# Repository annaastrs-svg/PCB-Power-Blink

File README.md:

Power Blink  ;)
---
A power bank PCB Module designed in KiCAD, to safly charge lithium battery and u can look in the display the battery percentage on the oled screen
o m g 

Power blink charges though USB-C and delivers power though USB-A, with an onboard fuel gauge and microcontroller driving a small OLED display that shows the actuall battery charge level :B 

BTW BTW BTW low key look at my [JOURNAL.MD WOOWOWOWOWOWWOWOOOO!](https://github.com/annaastrs-svg/PCB-Power-Blink/blob/Pcb/Journal.md)

KiCAD
--
Esquematico
--

PCB
--

3D VIEW 
--

PCB Huellas 
---

CAD
---

 CAD detailes :
 
 The PCB is 55.8067 mm long & 40.9582 tall so i added 2 mm in all sides so it can fit in 

 the button is 6x6 mm
 
 the oled is 5.584 & 22.384 long
 
 the entry of c 14.4 long 
 
 the entry of a is 8.94 cm long 
 
 (btw ignore the pcb it was a scratch )

[look CAD file ](https://github.com/annaastrs-svg/PCB-Power-Blink/tree/Pcb/CAD)

BOM 
---
[BOM file ](https://github.com/annaastrs-svg/PCB-Power-Blink/blob/Pcb/Documentation/BOM.csv)

| Component | Purpose | Qty | Price | link|
|---|---|---|---|---|
| LiPo Battery 3.7V | Fuente de energía principal | 1 | ~$2.29 | i alrdy have one lolazo |
| TP4056-42-ESOP8 | IC de carga | 1 | ~$0.09 | [LCSC C16581](https://www.lcsc.com/product-detail/Battery-Management-ICs_TOPPOWER-Nanjing-Extension-Microelectronics-TP4056-42-ESOP8_C16581.html) |
| DW01A-G | Controlador de protección | 1 | ~$0.07 | [LCSC C61503](https://www.lcsc.com/product-detail/C61503.html) |
| FS8205A | MOSFETs de protección | 1 | ~$0.03 | [LCSC C908265](https://www.lcsc.com/product-detail/MOSFETs_FUXINSEMI-FS8205A_C908265.html) |
| MAX17048G+T10 | Fuel gauge (I2C) | 1 | ~$1.34 | [LCSC C2682616](https://www.lcsc.com/product-detail/C2682616.html) |
| ATtiny1614-SSN | Microcontrolador | 1 | ~$1.67 | [LCSC C614832](https://www.lcsc.com/product-detail/Microcontroller-Units-MCUs-MPUs-SOCs_Microchip-Tech-ATTINY1614-SSN_C614832.html) |
| MT3608 | Boost converter a 5V | 1 | ~$0.11 | [LCSC C84817](https://www.lcsc.com/product-detail/C84817.html) |
| USB-C Receptacle (Hroparts) | Entrada de carga | 1 | ~$0.10 | [LCSC C165948](https://www.lcsc.com/product-detail/C165948.html) |
| USB-A Receptacle THT | Salida de energía | 1 | ~$0.15 | genérico, cualquier tienda |
| OLED 0.91" I2C SSD1306 | Pantalla de batería | 1 | ~$1.20 | [AliExpress](https://www.aliexpress.com/item/33024849277.html) |
| Pulsador momentáneo 6mm | Despertar pantalla | 1 | ~$0.05 | genérico |
| SS34 Schottky | Diodo del boost | 1 | ~$0.05 | genérico |
| LEDs indicadores (CHRG/STDBY) | Indicadores de carga | 2 | ~$0.02 ea. | genérico |
| Resistencias SMD (varias) | 5.1k, 4.7k, 2.4k, 470, 1k, 10k, 75k | 10 | ~$0.01 ea. | genérico |
| Capacitores SMD (10-22µF) | Desacople/filtro | 6 | ~$0.03 ea. | genérico |

**Estimated Total: ~$8.00 USD (sin batería yey )**

## Connection table
[also look at the connection table](https://github.com/annaastrs-svg/PCB-Power-Blink/blob/Pcb/Documentation/Tabla%20de%20Conexiones.csv)

| Componente | Pin | → | Componente | Pin |
|---|---|---|---|---|
| J3 (USB-C) | VBUS | → | U8 (TP4056) | VCC |
| J3 (USB-C) | CC1, CC2 | → | GND | (vía R1, R2 5.1k) |
| U8 (TP4056) | CE | → | VCC | |
| U8 (TP4056) | CHRG | → | LED D2 | → VCC |
| U8 (TP4056) | STDBY | → | LED D1 | → VCC |
| U8 (TP4056) | PROG | → | GND | (vía 2.4k) |
| U8 (TP4056) | BAT | → | +BATT (raw) | |
| Batería | + | → | Q1 (FS8205A) | S1 |
| Batería | − | → | GND | |
| Q1 (FS8205A) | S2 | → | −BATT | |
| Q1 (FS8205A) | G1 | → | U3 (DW01A) | OD |
| Q1 (FS8205A) | D1/D2 | → | U3 (DW01A) | CS (vía R6 1k) |
| Q1 (FS8205A) | G2 | → | U3 (DW01A) | OC |
| U3 (DW01A) | VCC | → | +BATT | (vía R5 470) |
| U3 (DW01A) | GND | → | −BATT | |
| U4 (MAX17048) | VDD | → | +BATT | |
| U4 (MAX17048) | GND | → | GND | |
| U4 (MAX17048) | SDA, SCL | → | Bus I2C | (compartido con U5, U6) |
| U5 (ATtiny1614) | VDD | → | +BATT | |
| U5 (ATtiny1614) | GND | → | GND | |
| U5 (ATtiny1614) | PA1 | → | Bus I2C | SDA |
| U5 (ATtiny1614) | PA2 | → | Bus I2C | SCL |
| U5 (ATtiny1614) | PA3 | → | SW1 | (botón) |
| U5 (ATtiny1614) | PA0/UPDI | → | J2 | Header de programación |
| Bus I2C | SDA, SCL | → | GND | (vía R9, R10 4.7k a +BATT) |
| U6 (OLED) | VCC | → | +BATT | |
| U6 (OLED) | GND | → | GND | |
| U6 (OLED) | SDA, SCL | → | Bus I2C | |
| U1 (MT3608) | IN | → | +BATT | |
| U1 (MT3608) | GND | → | GND | |
| U1 (MT3608) | SW | → | L1, D3 | → VOUT |
| U1 (MT3608) | FB | → | R7 (10k)/R8 (75k) | divisor |
| U1 (MT3608) | EN | → | +BATT | |
| J1 (USB-A) | VBUS | → | VOUT | |
| J1 (USB-A) | D+, D− | → | (puenteados entre sí) | |
| J1 (USB-A) | GND | → | GND | |

TUTORIAL & HOW DOES ITR WORK? HUH 
--

Open the Power Blinck file, the schematic, and the PCB in KiCad.
The symbols and footprints of the components are not included by default in KiCAS, but I attached the footprints and symbols in the PCB files. 
Add them as a library before opening the project, run the ERC and DRC to make sure everything is clean. 
To manufacture, use the Gerber files; they can be uploaded directly to PCBWay and like that :B

The circuit is divided into 4 blocks. The input and charging part is the USB-C, which receives the charge, and the TP4056, which safely charges the battery. (TP4056 SAFE)

The battery and protection section, with the DW01A and FS8205A, protects the cell against overcharge, overdischarge, and short circuits. (DW01A , FS8205A PROTECTS )

The monitoring is done by the MAX17048, which measures the battery percentage, and the ARINY1614, which displays it on the OLED screen. (MAX17048 MEASURE , ARINY1614 READS AND SHOW  )

The power output is the MT3608, which boosts the battery voltage to a stable 5V for the USB-A port. (MT3608 STABLE VOLTAGES)

i loved making this pcb cus it looks easy but at the moment u see a lot of chips/modules with a lot of pins u cant avoid panic
in my projects i struggle a lot with power distribution and this had helpped me a lot :B 

PCB WAY 
--
THIS IS THE V.1 OF THE PROJECT !! (I did it 2 times cus i didnt like v.1)

This is V.2 in PCB basics simulation of the pcb :B 

NOTES
---
This project was made for [MACONDO](https://macondo.hackclub.com/dashboard)

ill improve this project, there some things that ill change, maybe chips, modules or somthing like that. if u want to do this lil tutorial dont get mad at me if it doesnt work lolazo, Im 80 % sure it works !!

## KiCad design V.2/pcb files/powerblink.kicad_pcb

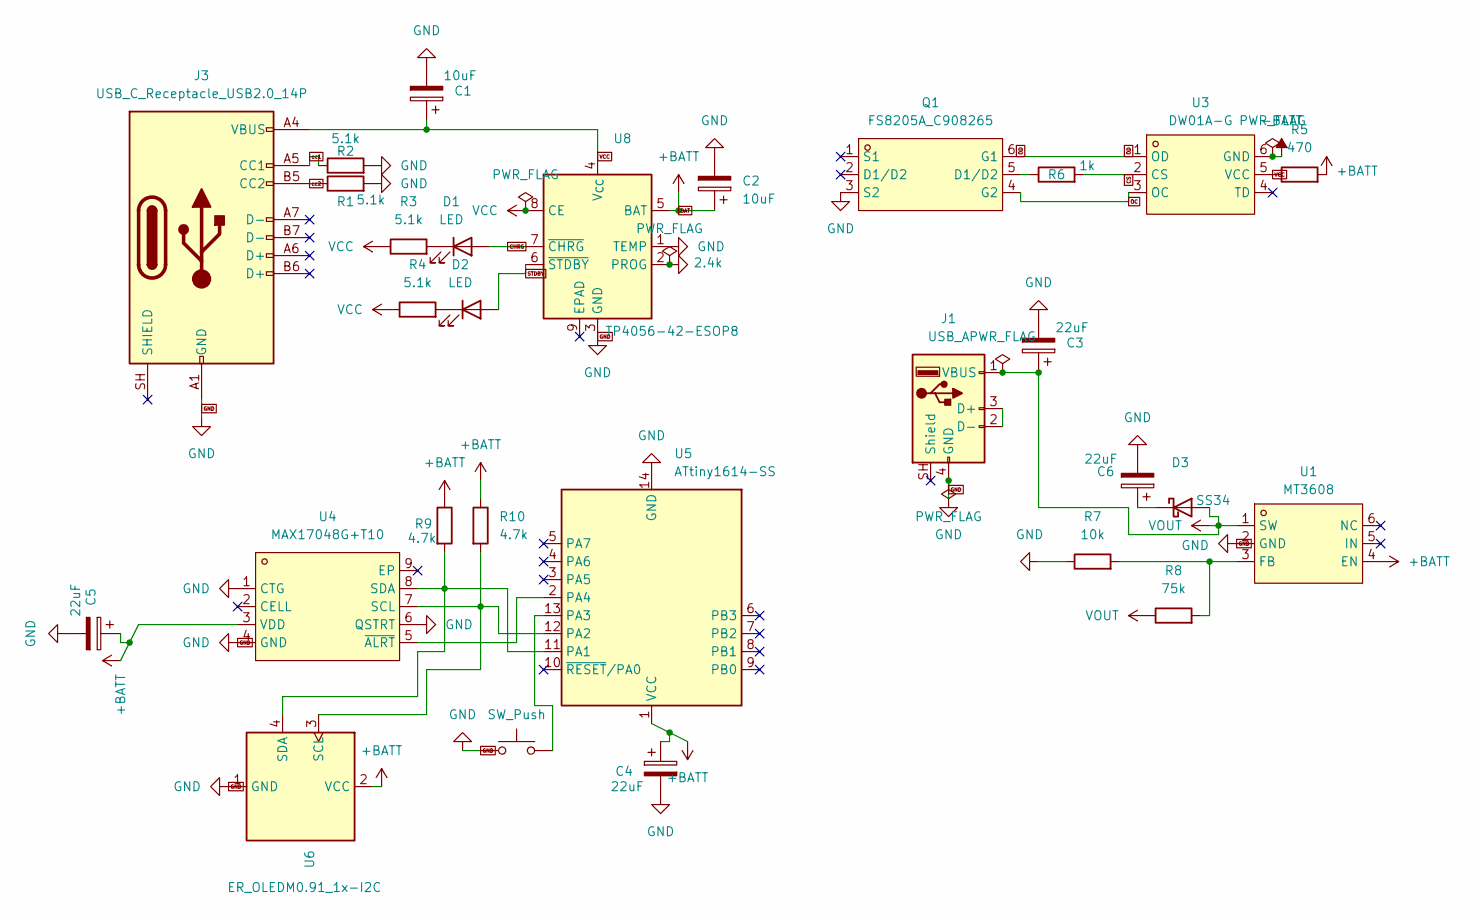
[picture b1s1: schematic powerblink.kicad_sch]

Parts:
C1, C2: 10uF; C_0805_2012Metric
C3, C4, C5, C6: 22uF; C_0805_2012Metric
D1, D2: LED; LED_0603_1608Metric
D3: SS34; D_SMA
J1: USB_A; USB3_A_Molex_48393-001
J3: USB_C_Receptacle_USB2.0_14P; USB_C_Receptacle_HRO_TYPE-C-31-M-12
Q1: FS8205A_C908265; SOT-23-6_L2.9-W1.6-P0.95-LS2.8-BR; MPN FS8205A; LCSC Part C908265
R1, R2, R3, R4: 5.1k; R_0603_1608Metric
R5: 470; R_0603_1608Metric
R6: 1k; R_0603_1608Metric
R7: 10k; R_0603_1608Metric
R8: 75k; R_0603_1608Metric
R9, R10: 4.7k; R_0603_1608Metric
SW1: SW_Push; SW_PUSH_6mm
U1: MT3608; SOT-23-6_L2.9-W1.6-P0.95-LS2.8-BL; MPN MT3608; LCSC Part C84817
U3: DW01A-G; SOT-23-6_L2.9-W1.6-P0.95-LS2.8-BR; MPN DW01A-G; LCSC Part C61503
U4: MAX17048G+T10; TDFN-8_L2.0-W2.0-P0.50-BL-EP1.2; MPN MAX17048G+T10; LCSC Part C2682616
U5: ATtiny1614-SS; SOIC-14_3.9x8.7mm_P1.27mm
U6: ER_OLEDM0.91_1x-I2C
U8: TP4056-42-ESOP8; SOIC-8-1EP_3.9x4.9mm_P1.27mm_EP2.41x3.3mm_ThermalVias

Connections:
2.4k: U8.2 (PROG)
-BATT: U3.6 (GND)
BAT: C2.1, C4.1, C5.1, R5.2, R9.1, R10.1, U1.4 (EN), U4.3 (VDD), U5.1 (VCC), U6.2 (VCC), U8.5 (BAT)
CHRG: D1.2 (A), U8.7 (~CHRG)
CS: R6.2, U3.2 (CS)
GND: C1.2, C2.2, C3.2, C4.2, C5.2, C6.2, J1.4 (GND), J3.A1 (GND), J3.A12 (GND), J3.B1 (GND), J3.B12 (GND), Q1.3 (S2), R1.2, R2.2, R7.1, SW1.1, U1.2 (GND), U4.1 (CTG), U4.4 (GND), U4.6 (QSTRT), U5.14 (GND), U6.1 (GND), U8.1 (TEMP), U8.3 (GND)
unnamed: D1.1 (K), R3.2
unnamed: D2.1 (K), R4.2
unnamed: C6.1, D3.1 (K)
unnamed: J1.2 (D-), J1.3 (D+)
unnamed: Q1.5 (D1/D2), R6.1
unnamed: R7.2, R8.2, U1.3 (FB)
unnamed: R10.2, U4.7 (SCL), U5.12 (PA2), U6.3 (SCL)
unnamed: R9.2, U4.8 (SDA), U5.11 (PA1), U6.4 (SDA)
unnamed: U4.5 (~ALRT), U5.2 (PA4)
unnamed: SW1.2, U5.13 (PA3)
OC: Q1.4 (G2), U3.3 (OC)
OD: Q1.6 (G1), U3.1 (OD)
STDBY: D2.2 (A), U8.6 (~STDBY)
VCC: C1.1, J3.A4 (VBUS), J3.A9 (VBUS), J3.B4 (VBUS), J3.B9 (VBUS), R3.1, R4.1, R5.1, U3.5 (VCC), U8.4 (V_{CC}), U8.8 (CE)
VOUT: C3.1, D3.2 (A), J1.1 (VBUS), R8.1, U1.1 (SW)
cc1: J3.A5 (CC1), R2.1
cc2: J3.B5 (CC2), R1.1

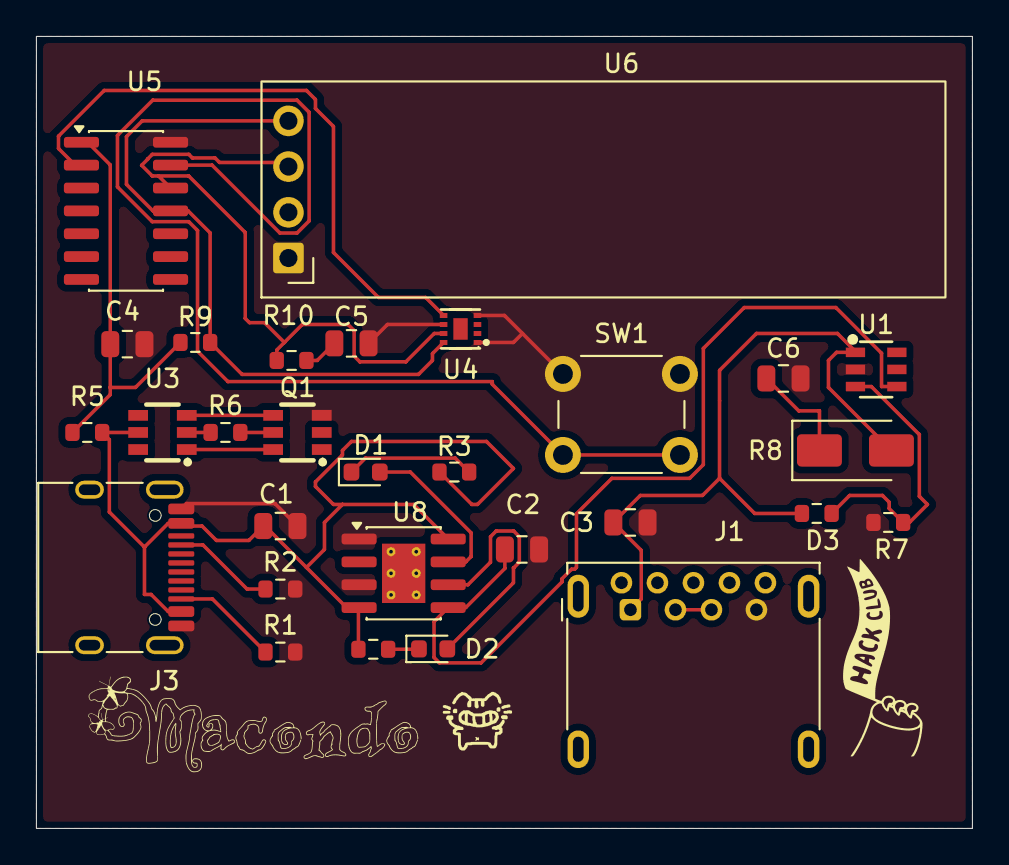
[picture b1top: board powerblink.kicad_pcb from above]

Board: 2 copper layers, 52.0 x 44.0 mm, 29 parts (0 on the bottom side), 21 nets.

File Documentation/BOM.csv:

Component,Purpose,Qty,Price,Product
LiPo Battery 3.7V,Fuente de energia principal,1,~$2.29,(ya la tienes)
TP4056-42-ESOP8,IC de carga,1,~$0.09,https://www.lcsc.com/product-detail/Battery-Management-ICs_T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
DW01A-G,Controlador de proteccion,1,~$0.07,https://www.lcsc.com/product-detail/C61503.html
FS8205A,MOSFETs de proteccion,1,~$0.03,https://www.lcsc.com/product-detail/MOSFETs_FUXINSEMI-FS8205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
MAX17048G+T10,Fuel gauge (I2C),1,~$1.34,https://www.lcsc.com/product-detail/C2682616.html
ATtiny1614-SSN,Microcontrolador,1,~$1.67,https://www.lcsc.com/product-detail/Microcontroller-Units-MC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
MT3608,Boost converter a 5V,1,~$0.11,https://www.lcsc.com/product-detail/C84817.html
USB-C Receptacle (Hroparts),Entrada de carga,1,~$0.10,https://www.lcsc.com/product-detail/C165948.html
USB-A Receptacle THT,Salida de energia,1,~$0.15,generico - cualquier tienda
OLED 0.91in I2C SSD1306,Pantalla de bateria,1,~$1.20,https://www.aliexpress.com/item/33024849277.html
Pulsador momentaneo 6mm,Despertar pantalla,1,~$0.05,generico
SS34 Schottky,Diodo del boost,1,~$0.05,generico
LEDs indicadores (CHRG/STDBY),Indicadores de carga,2,~$0.02 ea.,generico
Resistencias SMD varias,"5.1k, 4.7k, 2.4k, 470, 1k, 10k, 75k",10,~$0.01 ea.,generico
Capacitores SMD (10-22uF),Desacople/filtro,6,~$0.03 ea.,generico
